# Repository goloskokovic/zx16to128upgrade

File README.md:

# 128k RAM expansion for the ZX Spectrum 48k

<br/>

Upgrade ZX Spectrum 48k with 128kB of RAM and play games you couldn't play before. Sound will stay as before, but you can always build an [AY interface](https://github.com/goloskokovic/zx16to128upgrade/tree/main/AY) to sound like ZX Spectrum 128k. No need to change the ROM.

In order to make the RAM expansion work, a single wire mod to your ZX Spectrum 48k is required to disable the 32k upper RAM.
For Issue 2/3/4 connect pin 5 on IC23 (74LS32) to pin 14 (+5V). For Issue 5/6 connect pin 35 on IC27 (ZX8401) to pin 40 (+5V).
Both mods will hold the CAS/RAS signal high so it won't reach the RAM chips.
<br/>

Watch the video:

With this mod without the RAM expansion, your ZX Spectrum 48k will work as ZX Spectrum 16k.

To test the RAM expansion use modified [zx-diagnostics](/testram.tap) that allows you to manually select 128k test regardless of the ROM.

<br/>
<br/>
<br/>

<br/>
<br/>
GAL equations:

```
when 74HCT273_CLK is CLK7FFD
D0 is BANK0
D1 is BANK1
D2 is BANK2

CLK7FFD = /IORQ*/WR*/A15*A5*/A1
/RAMCS = /MREQ*A15
SA14 = A14*A15*BANK0
SA15 = A14*A15*BANK1 + /A14*A15
SA16 = A14*A15*BANK2
```
Original page: https://velesoft.speccy.cz/zx/external_128kb_upgrade/index.htm

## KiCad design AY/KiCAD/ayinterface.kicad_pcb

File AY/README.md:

# Simple AY interface

Part list:

1 x AY-3-8912

1 x 3.57954 MHz crystal

1 x 3,5mm jack socket PJ324

1 x 74LS138, 74LS00, 74LS74

2 x 1k resistor

2 x 1k6 resistor

5 x 470R resistor

2 x 100nF ceramic capacitor

2 x 4,7uF electrolytic capacitor

Original page:
https://www.zxsparrow.com/speccy_hw/simple/Simple_AY_IF/Simple_AY_IF_cze.html

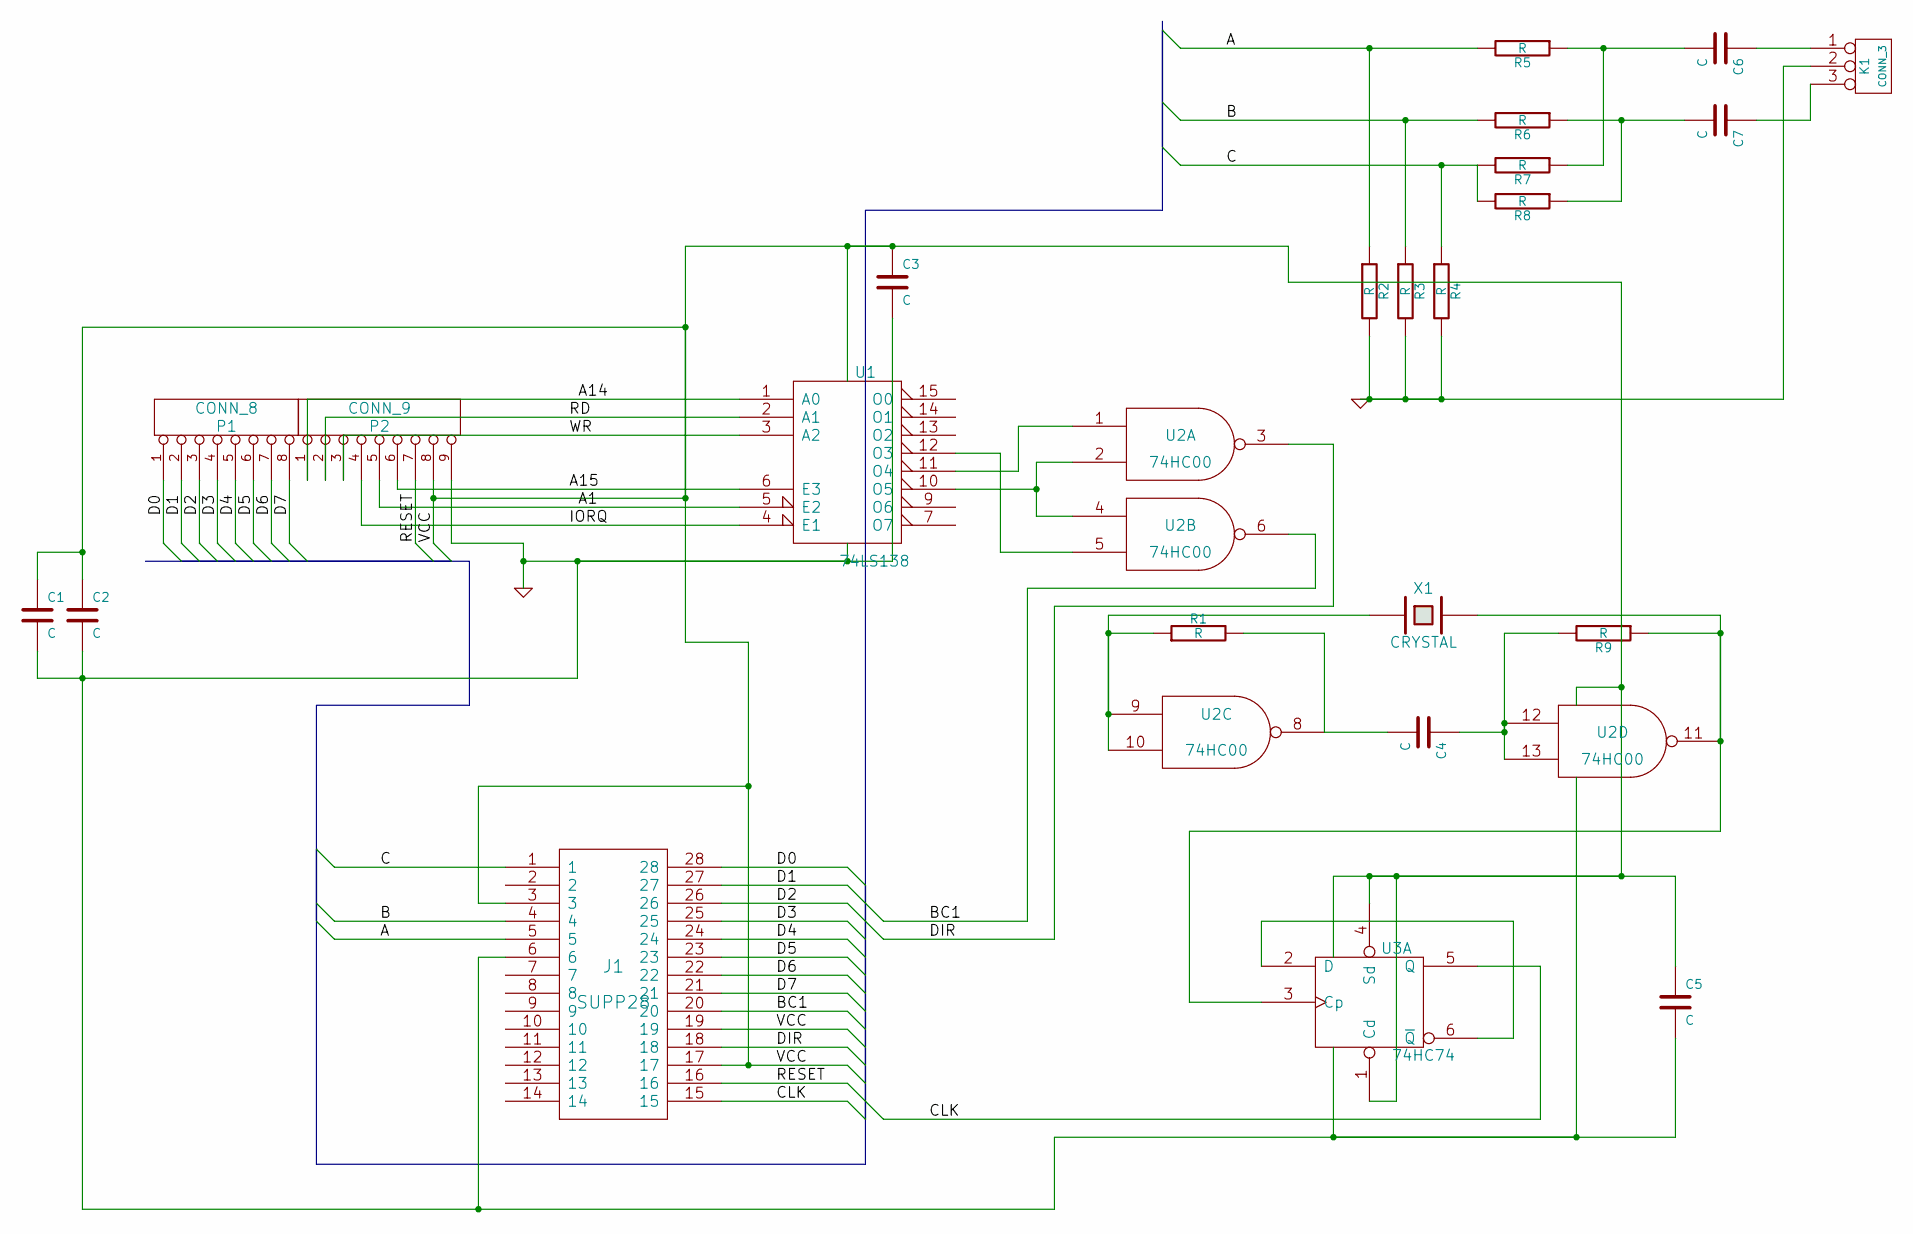
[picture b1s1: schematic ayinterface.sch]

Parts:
C1, C2, C3, C4, C5, C6, C7: C
J1: SUPP28
K1: CONN_3
P1: CONN_8
P2: CONN_9
R1, R2, R3, R4, R5, R6, R7, R8, R9: R
U1: 74LS138
U2: 74HC00
U3: 74HC74
X1: CRYSTAL

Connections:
/A: J1.5, R2.1, R5.2
/A1: P2.5, U1.5 (E2)
/A14: P2.1, U1.1 (A0)
/A15: P2.6, U1.6 (E3)
/B: J1.4, R3.1, R6.2
/BC1: J1.20, U2.6
/C: J1.1, R4.1, R7.2, R8.2
/CLK: J1.15, U3.5 (Q)
/D0: J1.28, P1.1
/D1: J1.27, P1.2
/D2: J1.26, P1.3
/D3: J1.25, P1.4
/D4: J1.24, P1.5
/D5: J1.23, P1.6
/D6: J1.22, P1.7
/D7: J1.21, P1.8
/DIR: J1.18, U2.3
/IORQ: P2.4, U1.4 (E1)
/RD: P2.2, U1.2 (A1)
/RESET: J1.16, P2.7
/WR: P2.3, U1.3 (A2)
GND: C1.2, C2.2, C3.2, C5.2, J1.6, K1.2 (PM), P2.9, R2.2, R3.2, R4.2, U1.8 (GND), U2.7 (GND), U3.7 (GND)
unnamed: C4.1, R9.2, U2.12, U2.13
unnamed: R9.1, U2.11, U3.3 (Cp), X1.2
unnamed: U1.11 (O4), U2.1
unnamed: C4.2, R1.2, U2.8
unnamed: C7.1, K1.3
unnamed: C7.2, R6.1, R8.1
unnamed: C6.1, K1.1
unnamed: C6.2, R5.1, R7.1
unnamed: U1.10 (O5), U2.2, U2.4
unnamed: U3.2 (D), U3.6 (~Q)
unnamed: R1.1, U2.9, U2.10, X1.1
unnamed: U1.12 (O3), U2.5
VCC: C1.1, C2.1, C3.1, C5.1, J1.3, J1.17, J1.19, P2.8, U1.16 (VCC), U2.14 (VCC), U3.1 (Cd), U3.4 (Sd), U3.14 (VCC)

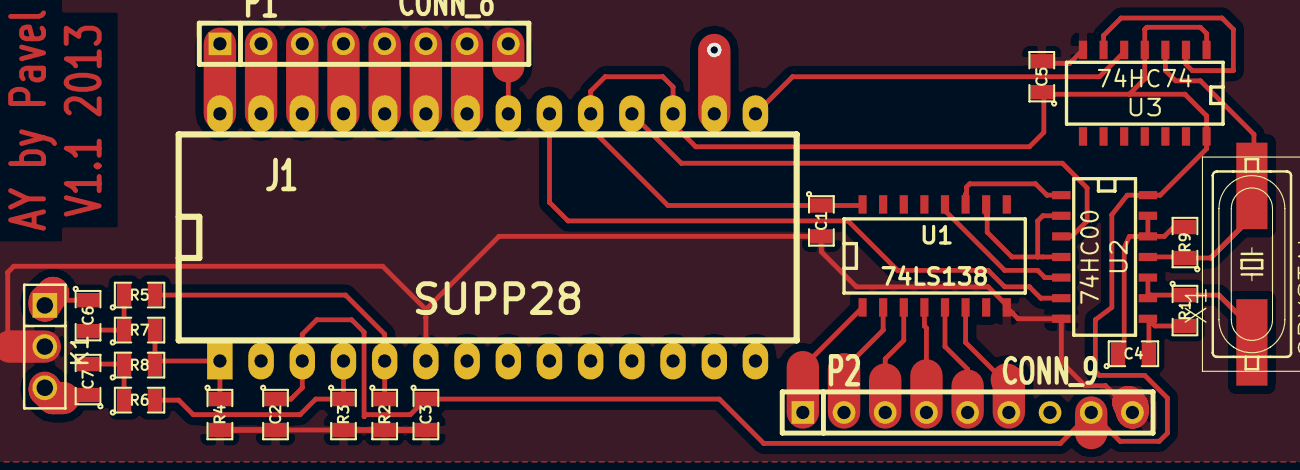
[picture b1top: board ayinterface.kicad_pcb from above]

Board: 2 copper layers, 24 parts (0 on the bottom side), 35 nets.

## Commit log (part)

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2022-10-09 48to128_mirror_gal20v8_firmware
2022-12-01 Rename MIRROR_.EQN to zx48_to_128-EASY_6b.eqn
2022-12-01 Rename MIRROR_.JED to zx48_to_128-EASY_6b.jed
2022-12-01 Rename MIRROR_.LOG to zx48_to_128-EASY_6b.log
2023-07-17 add gerber files
2023-08-29 Update to rev2
2023-08-29 add original image
2023-08-29 move PDF
2023-09-01 Update rm
2023-09-09 update md
2023-09-30 added AY pcbway project link
2023-10-04 pull up resistor comment
2023-10-15 simplify
2023-10-23 ver6 rev2
2024-01-16 7FFDh port
2024-01-29 7FFDh I/O port
2024-02-08 cas / ras
2024-02-08 CAS info
2024-02-10 CAS/RAS signal high
2024-02-15 manualy select 128k RAM test
2024-02-15 RAM test .tap
2024-02-16 Skip ROM check
2024-02-19 ver6 rev3
2024-02-26 ver6 rev4
2024-03-08 AY link
2024-03-08 bus extender
2024-03-09 reset switch
2024-04-14 new board
2024-06-15 test ram
2024-06-16 ground plane
2024-06-30 gerbers folder
2024-07-02 one wire mod
2024-07-02 rev2
2024-07-02 typo
2024-07-04 single wire mod
2024-09-13 v6c board
2025-02-18 equations
2025-09-04 GAL eq. update
2025-09-09 video
2025-09-29 resize images
2025-09-29 photo fix
2026-02-03 bom update
2026-02-08 photo update
2026-02-11 socket PJ324
